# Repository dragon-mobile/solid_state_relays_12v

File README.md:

# Solid State Relays - 12Volts

<br/>

<br/>

The Solid State Relays - 12Volts is one of the open hardware solid state relay
PCB of my Dragon Mobile GitHub organization with a goal to make
useful hardware with associated firmware and software for the tiny home, van
life and maker communities.

## Visual 3D examples

Top view<br/>
<br/>
Bottom view<br/>
<br/>

## Description

The board consist of three main electronic sections: Power In,
Control In / Power Out,
and the Solid State Relays which are divided into two banks of four output
channels.
There are two mechanical sections as well: Mounting Holes, and the
eight MOSFET Mounting Access Holes.

### Power In

The main 12 volt power source for the rest of the board enters via the
JPWR1 and optional JPWR2 XT-60PW-M connectors. Each is rated for up to 35A but
may support 40-50A loads for brief periods in practice with good cooling.
Care should be taken to not connect or disconnect the power when any outputs
are active as this may cause some arcing within the connector which will
shorten its life span. This will be especially noticable with large inductive
loads.

The two Transient-Voltage-Suppression (TVS) diodes: TVSP1 and optional TVSP2
provide protection against high voltage spikes from entering the board through
the power source. Additionally they can act as reverse polarity protection by
shorting the incorrectly wiring source and blow its fuse. Care should be taken
to ensure the 12 volt wire is properly fused.

The two optional fan connectors: M1 and M2 are avalible to add optional cooling
fans which are always on or use external temperature / speed control.
If enclosed in a tight fitting case or cover it's recommended that at least one
fan be used to prevent hot spots that can cause premature component failure or
in extereme cases fires.

The final part of the Power In section is the highly recommended but optional
power applied/on LED circuit. The LEDP1 should light up any time power is
connected to the board to give a quick visual indicator. Optionally the onboard
LED can be replaced by connecting an external LED via the optional JP2 pin
header. Connecting both LEDP1 and an external LED is not recommended. R1 is the
current limiting resistor for the LED and can be replaced with 0Ω one when
an external resistor is used on the JP2 circuit.
By cutting the trace between the pads of JP1 the indicator circuit can be
disabled. Additionally by doing this and soldering two leads to the pads an
external switch could be used to turn the indicator on and off as needed.

#### Optional components

The board is design to supply 30-40A across all outputs without the addition
of JPWR2 and TVSP2 to save costs. For higher currents both the additional
connector and TVS should be used. It is also recommended you increase the
board copper plating to 3oz (105μm). An alternative but not recommended and
more risky way to increase current capacity is by soldering some point to point
jumper wires from near the power connectors and the center lead of the output
FETs and from the output of the FETs to the leads of the output connectors.

TVSP2 is the only surface mount component on the bottom side of the board.

### Control In / Power Out

This section provides the connectors JCNTL1 and JCNTL2 which interfaces the
control signals from the external circuits to the output FETs.
The external controls should be either electronic open drain (collector) or
mechanical switches which pull their output to ground when active.
The external controls may also switch between the +BATT voltage and ground but
an active low only signal is expected and preferred when possible.
Each connector is connected to a single bank of 4 output channels allowing each
one to be used with a different control if needed though a single control
connected to and controlling both is the expected configuration.

Additionally the connectors can each be used to supply power of +BATT volts at
1A max to external circuits.
Normally this is used to supply power to an external control boards like the
co-designed and recommended [picow_ssr_control] or [we_ssr_control] boards.

### Solid State Relays

This is the main section of the circuit board and contains most of the
components. There are 8 independent solid state relay circuits which are
designed to work the same. The relays outputs are laid out as two banks of
four channels each on the two longer edges of the board to allow easy access.
A single channel will be described next since other than their position and
names etc. the design is the same.

#### Channel description

The OUT1 channel will be used in this description. The switching (relay)
component is Q1 a P-channel IRF4905 MOSFET which electrical connects the +BATT
voltage to the output connector J1 (OUT1) when activated. The pullup resistor
RP1 keeps the FET off when there is no low input driving the gate via the
control input from the a1 pin of the JCNTL1 connector. The expected control
input is a open drain (collector) output which only actively drives the input
to ground and allows its output to float otherwise.

*Note* that Q1 is mounted on the bottom side of the board and bent over to
allow easy attachment to a large heat sink which is required. Look at the
picture of the bottom of the board in the Visual 3D examples section of this
README to better understand what it looks like when bent over for mounting.

** WARNING ** the metal tab and back of Q1 are at +BATT and need to be
electrically isolated from the heat sink if it is grounded while still
maintaining a good thermal contact.

The output is protected from most high voltage and reverse voltage spikes by
TVS1 a unidirectional Transient-Voltage-Suppression diode. It is mostly there
to protect against ESD and the voltage spikes commonly seens when switch off
inductive loads which could damage Q1 if they exceeded its own internal
protections.

The final three components: RL1, LED1, and the optional JL1 provide a quick
visual indicator for when the output is active. RL1 is the current limiting
resistor for the LED. Like with the power indicator circuit the indicator
circuit is all optional but highly recommended. When an LED is connected via
JL1 the internal LED should not be used.

### Mounting Holes

A US letter sized mounting template can be found in [MountingTemplate].

In a typical application the board will be mounted with brass or stainless
steel standoff which are tapped into a vertical aluminum, copper, or brass
backplate which also acts as the heat sink for the output FETs and all of
this is inside of a larger electrical enclosure or cabinet.
The mounting holes are sized for M3 hex (preferred) or round Male-Female ended
standoffs which should be 5-10mm high to allow the correct mounting of the
output FETs. the shortest standoff that doesn't cause the body to contact the
board and allow the legs to be bent at a right angle just pass the "neck" is
best.
In most cases this should be 5-6mm high but can end up as high as 10mm
depending on the insulators used.

The [picow_ssr_control] and [we_ssr_control] boards have been designed to mount
directly on top of / in front of this board with additional 20mm M-F standoffs
which would replace the normal M3 pan head screws used to secure the board at
H1, H4, and H5.

### MOSFET Mounting Access Holes

The last mechanical section are the access holes that were added to make
mounting the FET to an underlaying heat sink easier. They can also be found
on the [MountingTemplate]. On the template you will see outlines for a
typical silicone insulators.

*Note* one top corner of the HQ2 and HQ6 insulators may interfere with mounting
hole H5 and need to be trimmed back or bent up a little if flexible enough to
allow complete tighten of the standoff and not cause the board to bow up in the
middle. By using a magnetic screwdriver you should be able to pass the screw,
lock, and plastic shoulder washers through the holes in the board and FET to be
tighten down.
A little silicone or thermal grease can help keep the washers in place without
cause other issues.

## Contributing

Contributors are welcome.
Please note that this project has a [Contributor Covenant Code of Conduct].
By participating in this project you agree to abide by its terms.

All intentionally contributed hardware will be considered to be contributed
under the [CERN] license without any additional terms or conditions.

All intentionally contributed code will be considered to be contributed
under a [MIT] license without any additional terms or conditions.
Please include your information in a comment on all code files for the copyright
etc.

All intentionally contributed documentation, CAD files and libraries, footprints,
artwork or non-code text like this README etc. will be considered to be
contributed under the same [CC-BY-SA] license without any additional terms or
conditions.

Pull requests are always welcome. For major changes, please open an issue first
to discuss what you would like to change.
Please make sure to update or add tests as appropriate for all software changes.

## Licenses

<br/>

All hardware is licensed under the

  * [CERN] - CERN-OHL-W-2.0
  
You can find a copy of the CERN Open Hardware License - Weakly-reciprocal v2.0
in the [LICENSE-CERN-OHL-W-2] file and the how-to guide in the
[CERN-HOWTO_GUIDE] file.

All code is licensed under the

  * [MIT] - MIT License

You can find a copy of the license in the [LICENSE-MIT] file.

All documentation like this README is licensed under the Creative Commons
Attribution-ShareAlike 4.0 International License (CC-BY-SA).

All original CAD files and libraries, footprints, and artwork are also licensed
under the
Creative Commons Attribution-ShareAlike 4.0 International License (CC-BY-SA).
You can find a copy of the [CC-BY-SA] license in the [LICENSE-CC-BY-SA] file.

If after reading the above license files, how-tos, and related FAQs on the
linked license sites on how they apply to the project please either open an
issue or contact me (Michael Cummings) via my Github email and I will try
to guided you through my understanding of how it works.

[CC-BY-SA]: http://creativecommons.org/licenses/by-sa/4.0/
[CERN]: https://ohwr.org/project/cernohl/wikis/Documents/CERN-OHL-version-2
[CERN-HOWTO_GUIDE]: docs/cern_ohl_w_v2_howto.pdf
[Contributor Covenant Code of Conduct]: CODE_OF_CONDUCT.md 
[LICENSE-CC-BY-SA]: LICENSE-CC-BY-SA
[LICENSE-CERN-OHL-W-2]: CERN-OHL-W-2
[LICENSE-MIT]: LICENSE-MIT
[MIT]: https://opensource.org/licenses/MIT
[MountingTemplate]: docs/MountingTemplate.pdf
[picow_ssr_control]: https://github.com/dragon-mobile/picow_ssr_control
[we_ssr_control]: https://github.com/dragon-mobile/we_ssr_control

<hr>
Copyright &copy; 2022-2023, Michael Cummings<br/>

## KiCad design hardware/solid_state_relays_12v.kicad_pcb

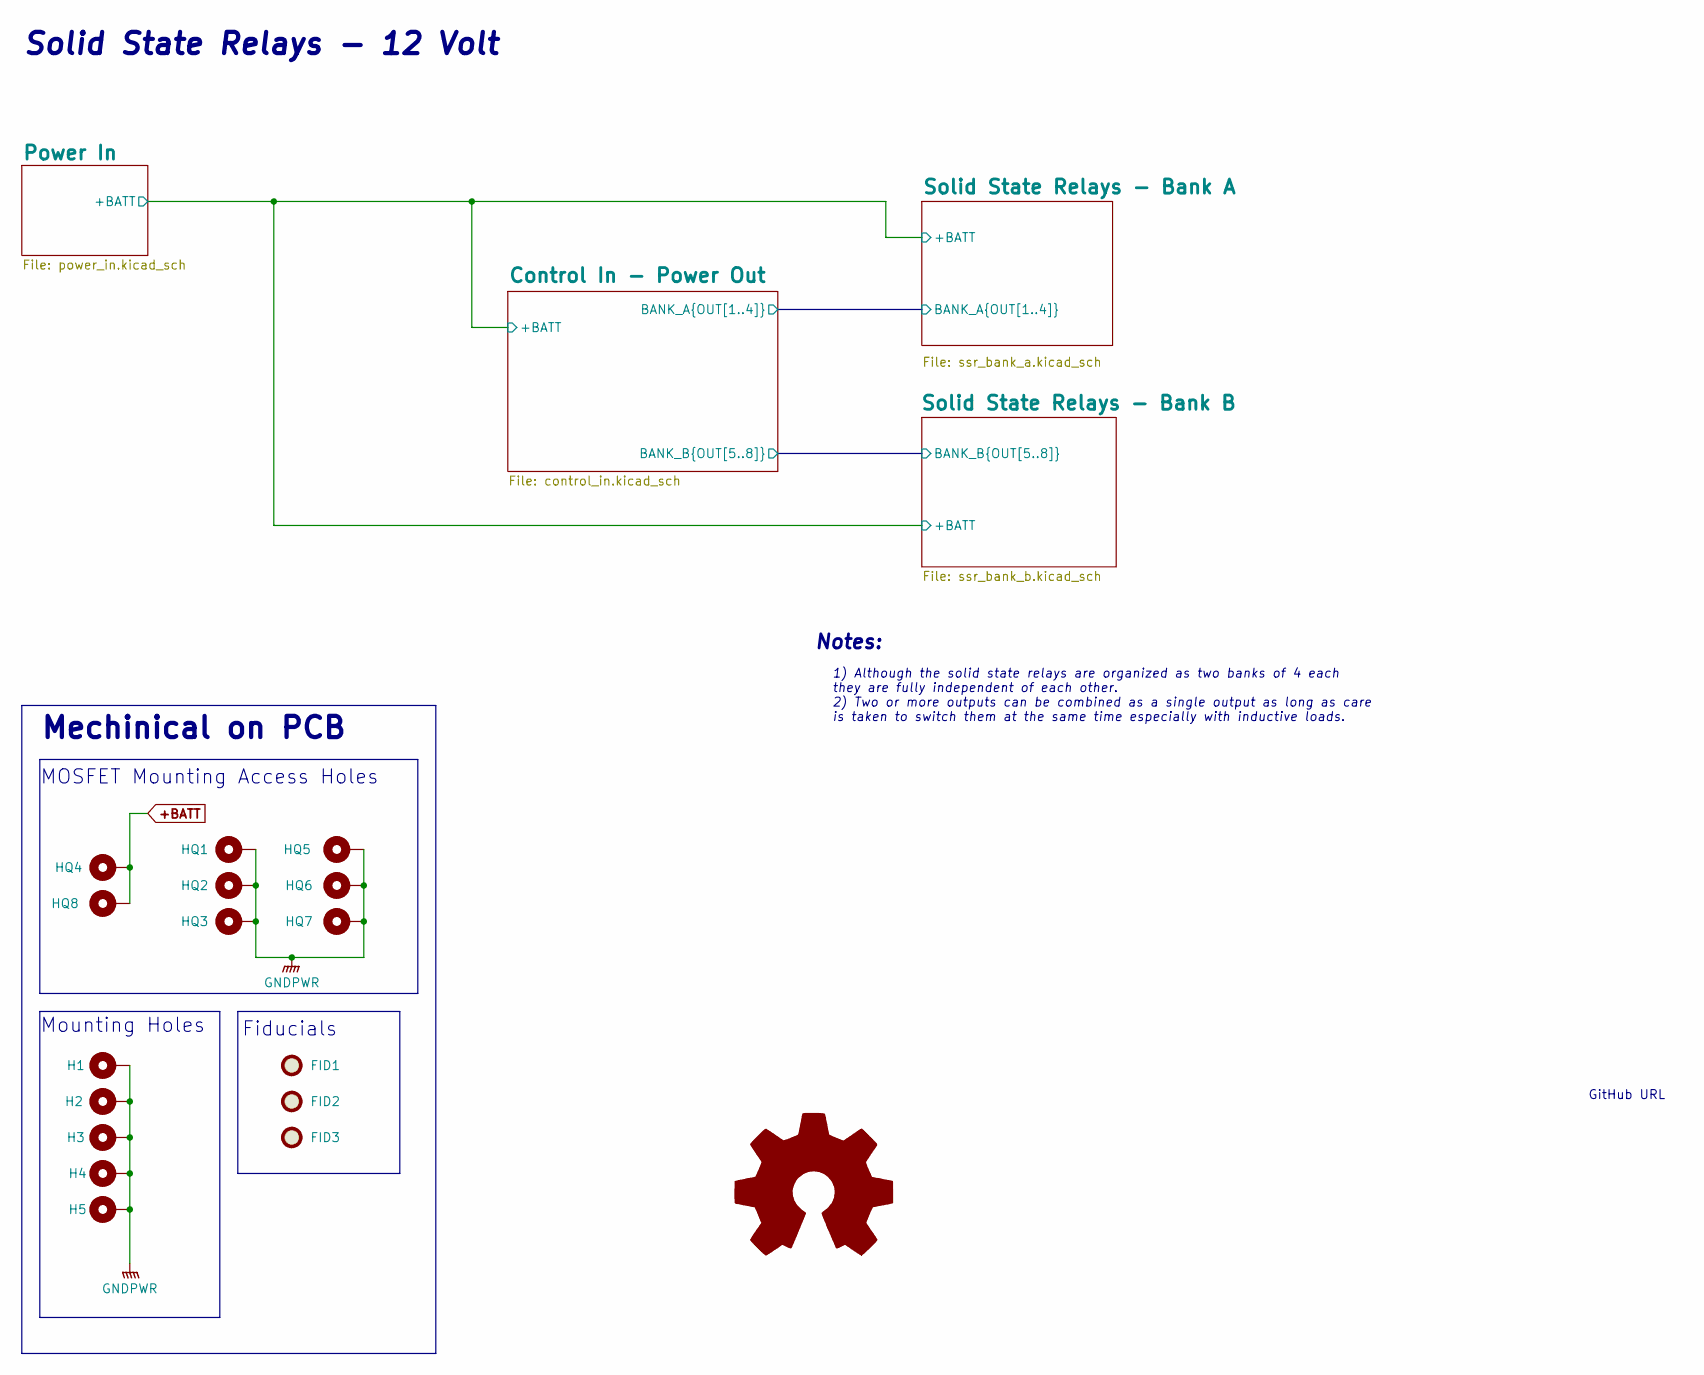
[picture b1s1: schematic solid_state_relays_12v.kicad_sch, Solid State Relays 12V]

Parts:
FID1, FID2, FID3: Fiducial; Fiducial_0.5mm_Mask1mm
H1, H2, H3, H4, H5: MountingHole; MountingHole_3.2mm_M3_Pad_Via
HQ1, HQ2, HQ3, HQ4, HQ5, HQ6, HQ7, HQ8: Access Hole; MountingHole_6.1mm_Pad_Via

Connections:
+BATT: HQ4.1, HQ8.1; also elsewhere on the board
GNDPWR: H1.1, H2.1, H3.1, H4.1, H5.1, HQ1.1, HQ2.1, HQ3.1, HQ5.1, HQ6.1, HQ7.1; also elsewhere on the board

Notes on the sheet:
MOSFET Mounting Access Holes
Fiducials
Solid State Relays - 12 Volt
Notes:
Mechinical on PCB
Mounting Holes
GitHub URL
1) Although the solid state relays are organized as two banks of 4 each they are fully independent of each other. 2) Two or more outputs can be combined as a single output as long as care is taken to switch them at the same time especially with inductive loads.

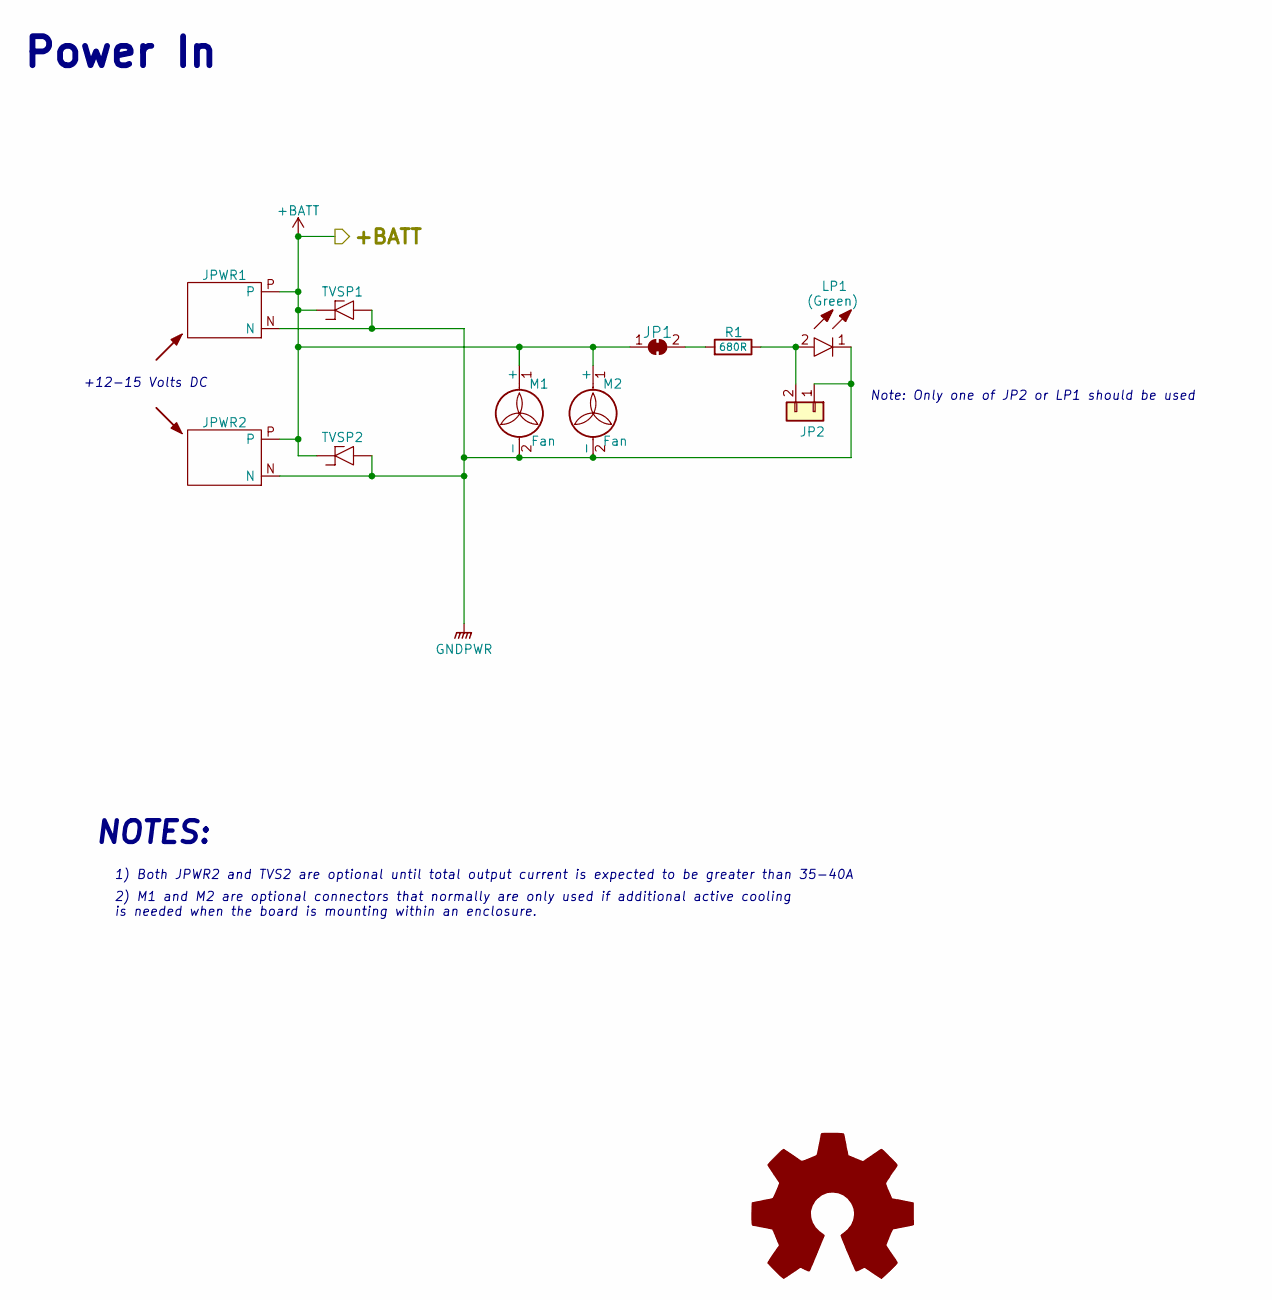
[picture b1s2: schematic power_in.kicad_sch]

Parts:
JP1: SolderJumper_2_Bridged; SolderJumper-2_P1.3mm_Bridged_RoundedPad1.0x1.5mm
JP2: Conn_01x02; PinHeader_1x02_P1.00mm_Vertical
JPWR1, JPWR2: XT60PW-M; XT60PWM
LP1: LTST-C190KGKT; LEDC1608X80N; Mouser Part Number 859-LTST-C190KGKT
M1, M2: Fan; PinHeader_1x02_P2.54mm_Vertical
R1: 680R; R_0805_2012Metric; Mouser Part Number 755-SDR10EZPJ681
TVSP1, TVSP2: SM6T18AY; Mouser Part Number 511-SM6T18AY

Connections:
+BATT: JP1.1 (A), JPWR1.P, JPWR2.P, M1.1 (+), M2.1 (+), TVSP1.1, TVSP2.1; also elsewhere on the board
GNDPWR: JP2.1, JPWR1.N, JPWR2.N, LP1.1, M1.2 (-), M2.2 (-), TVSP1.2, TVSP2.2; also elsewhere on the board
unnamed: JP1.2 (B), R1.2
unnamed: JP2.2, LP1.2, R1.1

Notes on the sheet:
Power In
Note: Only one of JP2 or LP1 should be used
1) Both JPWR2 and TVS2 are optional until total output current is expected to be greater than 35-40A
+12-15 Volts DC
2) M1 and M2 are optional connectors that normally are only used if additional active cooling is needed when the board is mounting within an enclosure.
NOTES:

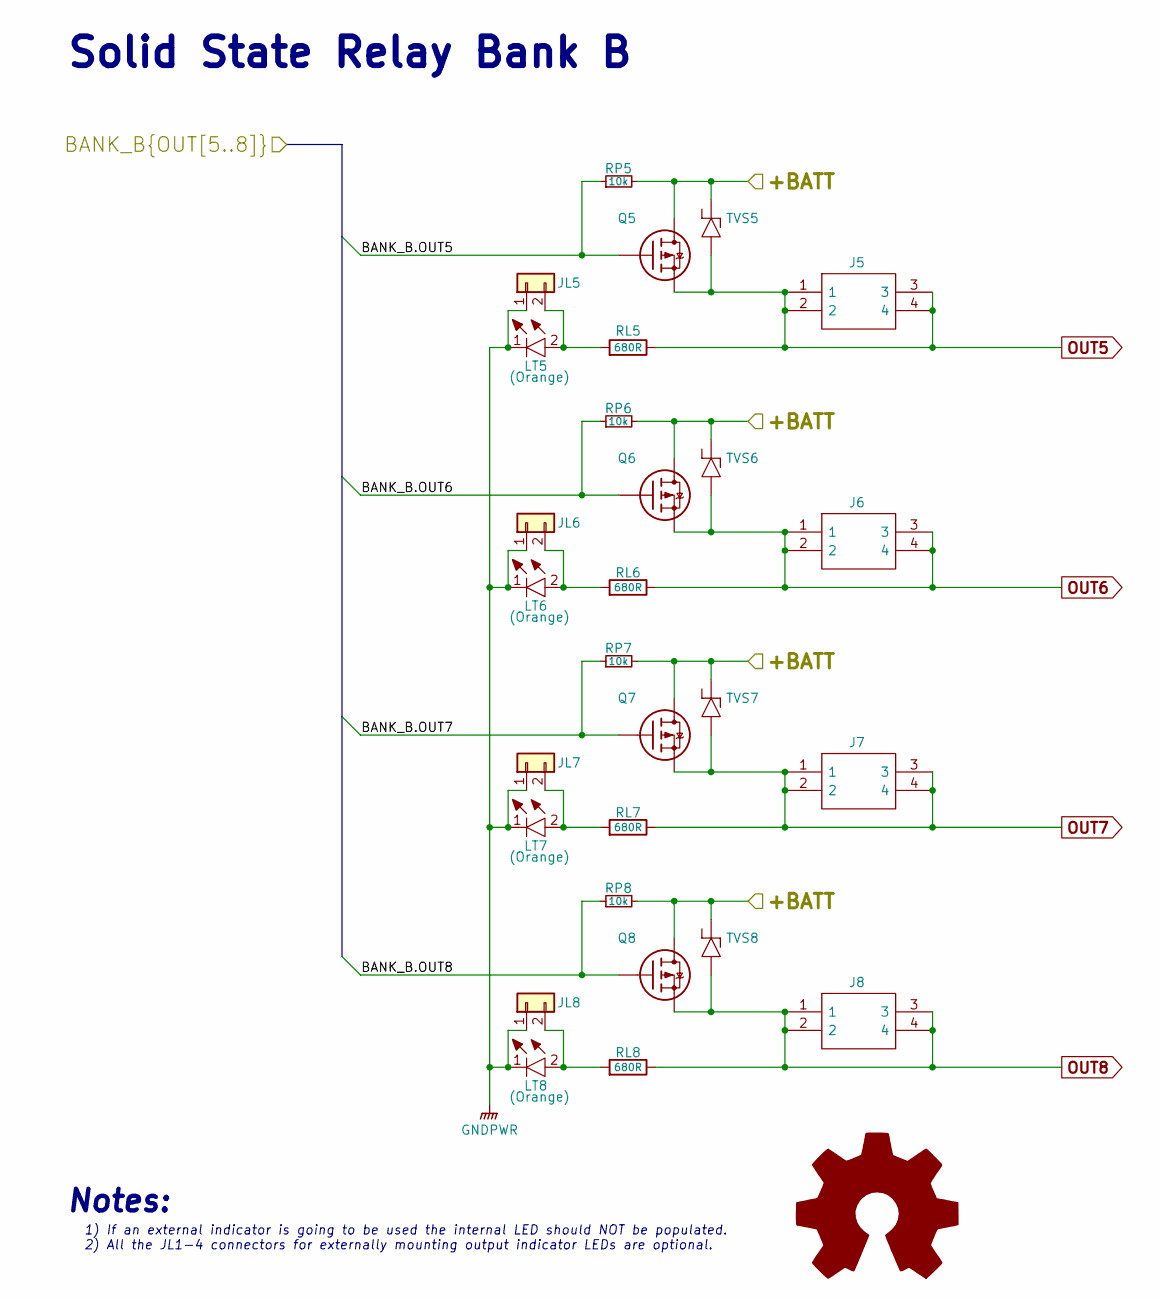
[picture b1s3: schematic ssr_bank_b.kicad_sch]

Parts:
J5, J6, J7, J8: 1190297; Mouser Part Number 651-1190297
JL5, JL6, JL7, JL8: Conn_01x02; PinHeader_1x02_P1.00mm_Vertical
LT5, LT6, LT7, LT8: LTST-C190KFKT; LEDC1607X80N; Mouser Part Number 859-LTST-C190KFKT
Q5, Q6, Q7, Q8: IRF4905PBF; Mouser Part Number 942-IRF4905PBF
RL5, RL6, RL7, RL8: 680R; R_0805_2012Metric; Mouser Part Number 755-SDR10EZPJ681
RP5, RP6, RP7, RP8: 10k; R_0603_1608Metric
TVS5, TVS6, TVS7, TVS8: SM6T18AY; Mouser Part Number 511-SM6T18AY

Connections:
+BATT: Q5.2, Q6.2, Q7.2, Q8.2, RP5.2, RP6.2, RP7.2, RP8.2, TVS5.1, TVS6.1, TVS7.1, TVS8.1; also elsewhere on the board
/Control In - Power Out/BANK_B.OUT5: Q5.1, RP5.1; also elsewhere on the board
/Control In - Power Out/BANK_B.OUT6: Q6.1, RP6.1; also elsewhere on the board
/Control In - Power Out/BANK_B.OUT7: Q7.1, RP7.1; also elsewhere on the board
/Control In - Power Out/BANK_B.OUT8: Q8.1, RP8.1; also elsewhere on the board
GNDPWR: JL5.1, JL6.1, JL7.1, JL8.1, LT5.1, LT6.1, LT7.1, LT8.1; also elsewhere on the board
unnamed: JL5.2, LT5.2, RL5.2
unnamed: JL6.2, LT6.2, RL6.2
unnamed: JL7.2, LT7.2, RL7.2
unnamed: JL8.2, LT8.2, RL8.2
OUT5: J5.1, J5.2, J5.3, J5.4, Q5.3, RL5.1, TVS5.2
OUT6: J6.1, J6.2, J6.3, J6.4, Q6.3, RL6.1, TVS6.2
OUT7: J7.1, J7.2, J7.3, J7.4, Q7.3, RL7.1, TVS7.2
OUT8: J8.1, J8.2, J8.3, J8.4, Q8.3, RL8.1, TVS8.2

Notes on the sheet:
Notes:
Solid State Relay Bank B
1) If an external indicator is going to be used the internal LED should NOT be populated. 2) All the JL1-4 connectors for externally mounting output indicator LEDs are optional.

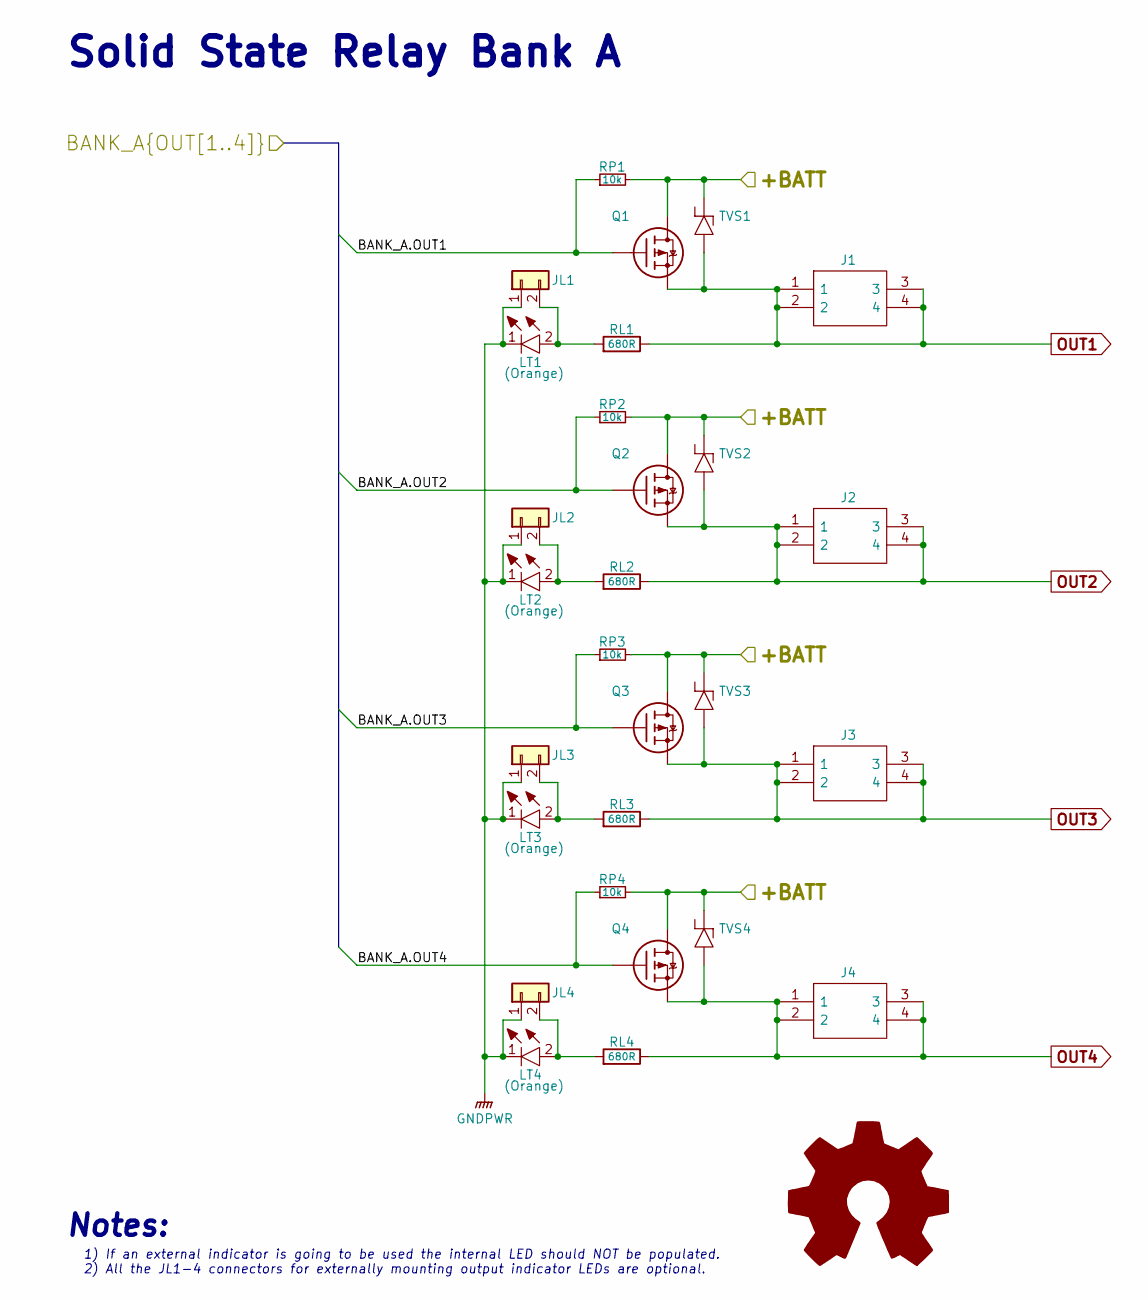
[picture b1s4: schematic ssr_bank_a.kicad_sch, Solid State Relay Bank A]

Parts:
J1, J2, J3, J4: 1190297; Mouser Part Number 651-1190297
JL1, JL2, JL3, JL4: Conn_01x02; PinHeader_1x02_P1.00mm_Vertical
LT1, LT2, LT3, LT4: LTST-C190KFKT; LEDC1607X80N; Mouser Part Number 859-LTST-C190KFKT
Q1, Q2, Q3, Q4: IRF4905PBF; Mouser Part Number 942-IRF4905PBF
RL1, RL2, RL3, RL4: 680R; R_0805_2012Metric; Mouser Part Number 755-SDR10EZPJ681
RP1, RP2, RP3, RP4: 10k; R_0603_1608Metric
TVS1, TVS2, TVS3, TVS4: SM6T18AY; Mouser Part Number 511-SM6T18AY

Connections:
+BATT: Q1.2, Q2.2, Q3.2, Q4.2, RP1.2, RP2.2, RP3.2, RP4.2, TVS1.1, TVS2.1, TVS3.1, TVS4.1; also elsewhere on the board
/Control In - Power Out/BANK_A.OUT1: Q1.1, RP1.1; also elsewhere on the board
/Control In - Power Out/BANK_A.OUT2: Q2.1, RP2.1; also elsewhere on the board
/Control In - Power Out/BANK_A.OUT3: Q3.1, RP3.1; also elsewhere on the board
/Control In - Power Out/BANK_A.OUT4: Q4.1, RP4.1; also elsewhere on the board
GNDPWR: JL1.1, JL2.1, JL3.1, JL4.1, LT1.1, LT2.1, LT3.1, LT4.1; also elsewhere on the board
unnamed: JL1.2, LT1.2, RL1.2
unnamed: JL2.2, LT2.2, RL2.2
unnamed: JL3.2, LT3.2, RL3.2
unnamed: JL4.2, LT4.2, RL4.2
OUT1: J1.1, J1.2, J1.3, J1.4, Q1.3, RL1.1, TVS1.2
OUT2: J2.1, J2.2, J2.3, J2.4, Q2.3, RL2.1, TVS2.2
OUT3: J3.1, J3.2, J3.3, J3.4, Q3.3, RL3.1, TVS3.2
OUT4: J4.1, J4.2, J4.3, J4.4, Q4.3, RL4.1, TVS4.2

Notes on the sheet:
Notes:
Solid State Relay Bank A
1) If an external indicator is going to be used the internal LED should NOT be populated. 2) All the JL1-4 connectors for externally mounting output indicator LEDs are optional.

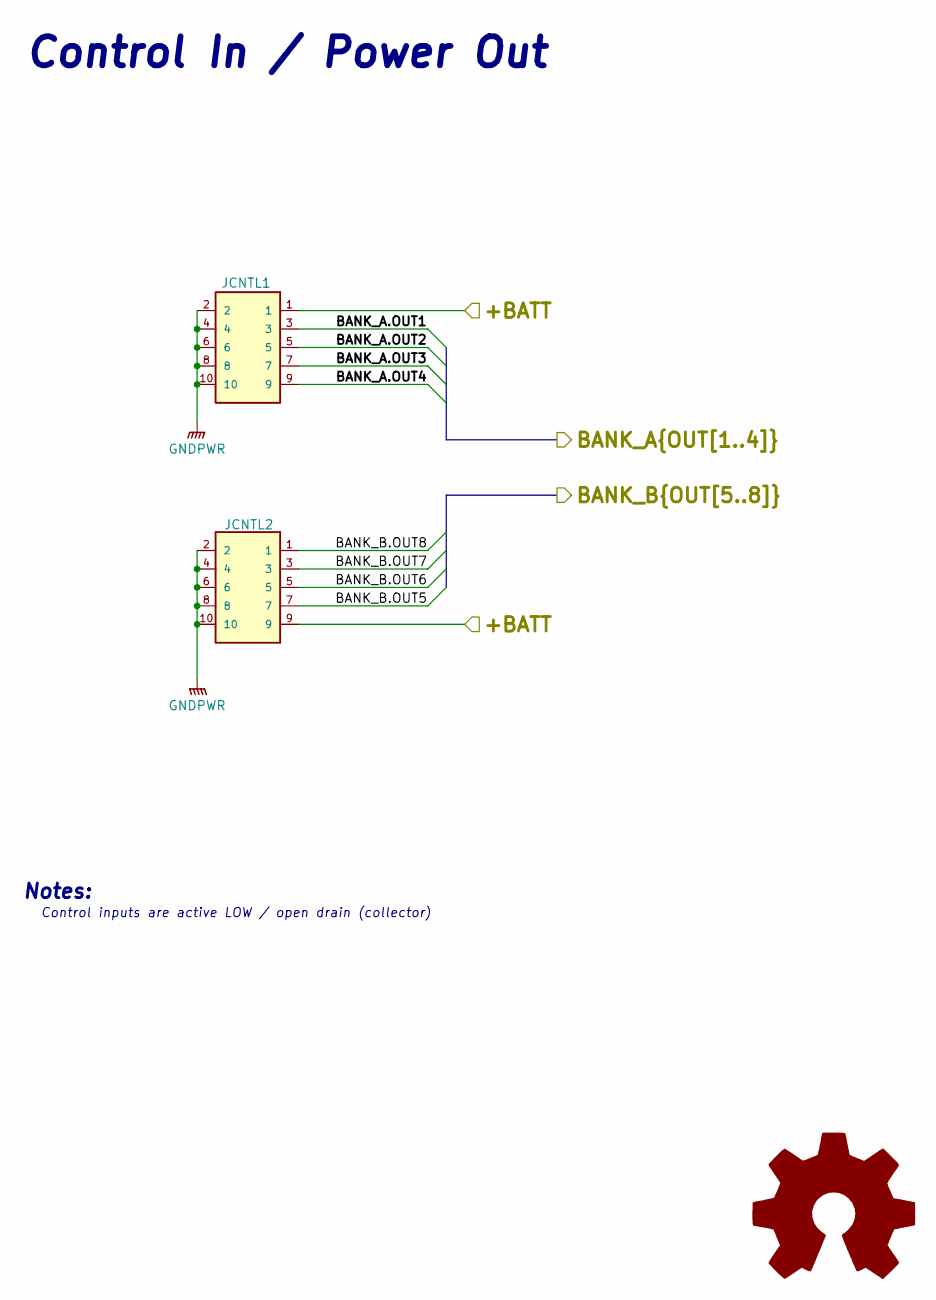
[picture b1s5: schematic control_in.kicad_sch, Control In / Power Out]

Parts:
JCNTL1, JCNTL2: SHF-105-01-L-D-RA; SAMTEC_SHF-105-01-L-D-RA; Mouser Part Number 200-SHF10501LDRATR

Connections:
+BATT: JCNTL1.1, JCNTL2.9; also elsewhere on the board
/Control In - Power Out/BANK_A.OUT1: JCNTL1.3; also elsewhere on the board
/Control In - Power Out/BANK_A.OUT2: JCNTL1.5; also elsewhere on the board
/Control In - Power Out/BANK_A.OUT3: JCNTL1.7; also elsewhere on the board
/Control In - Power Out/BANK_A.OUT4: JCNTL1.9; also elsewhere on the board
/Control In - Power Out/BANK_B.OUT5: JCNTL2.7; also elsewhere on the board
/Control In - Power Out/BANK_B.OUT6: JCNTL2.5; also elsewhere on the board
/Control In - Power Out/BANK_B.OUT7: JCNTL2.3; also elsewhere on the board
/Control In - Power Out/BANK_B.OUT8: JCNTL2.1; also elsewhere on the board
GNDPWR: JCNTL1.2, JCNTL1.4, JCNTL1.6, JCNTL1.8, JCNTL1.10, JCNTL2.2, JCNTL2.4, JCNTL2.6, JCNTL2.8, JCNTL2.10; also elsewhere on the board

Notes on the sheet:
Notes:
Control inputs are active LOW / open drain (collector)
Control In / Power Out

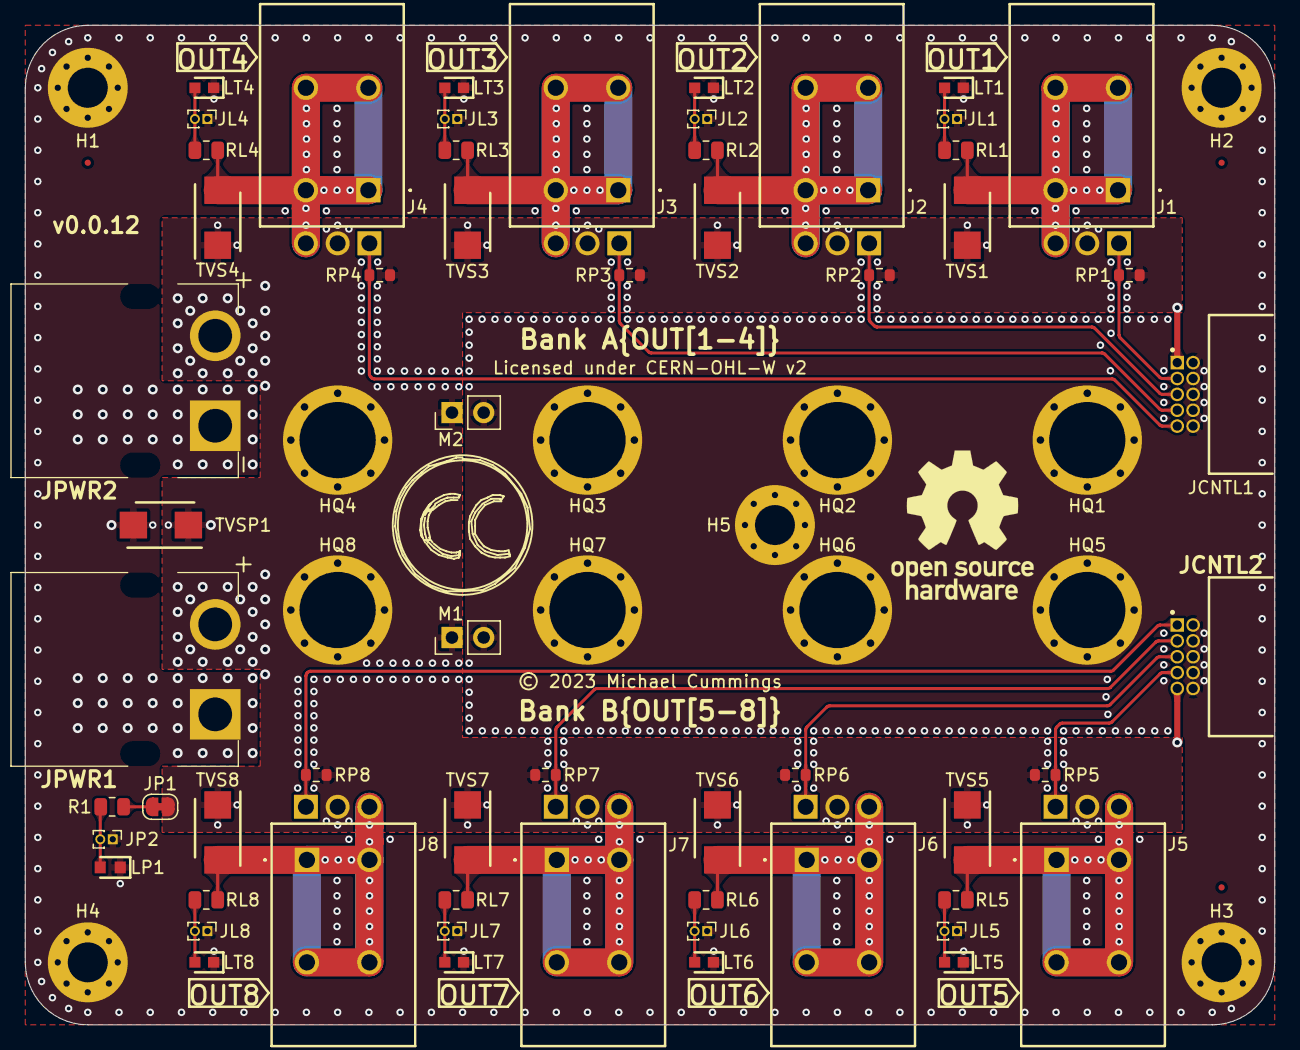
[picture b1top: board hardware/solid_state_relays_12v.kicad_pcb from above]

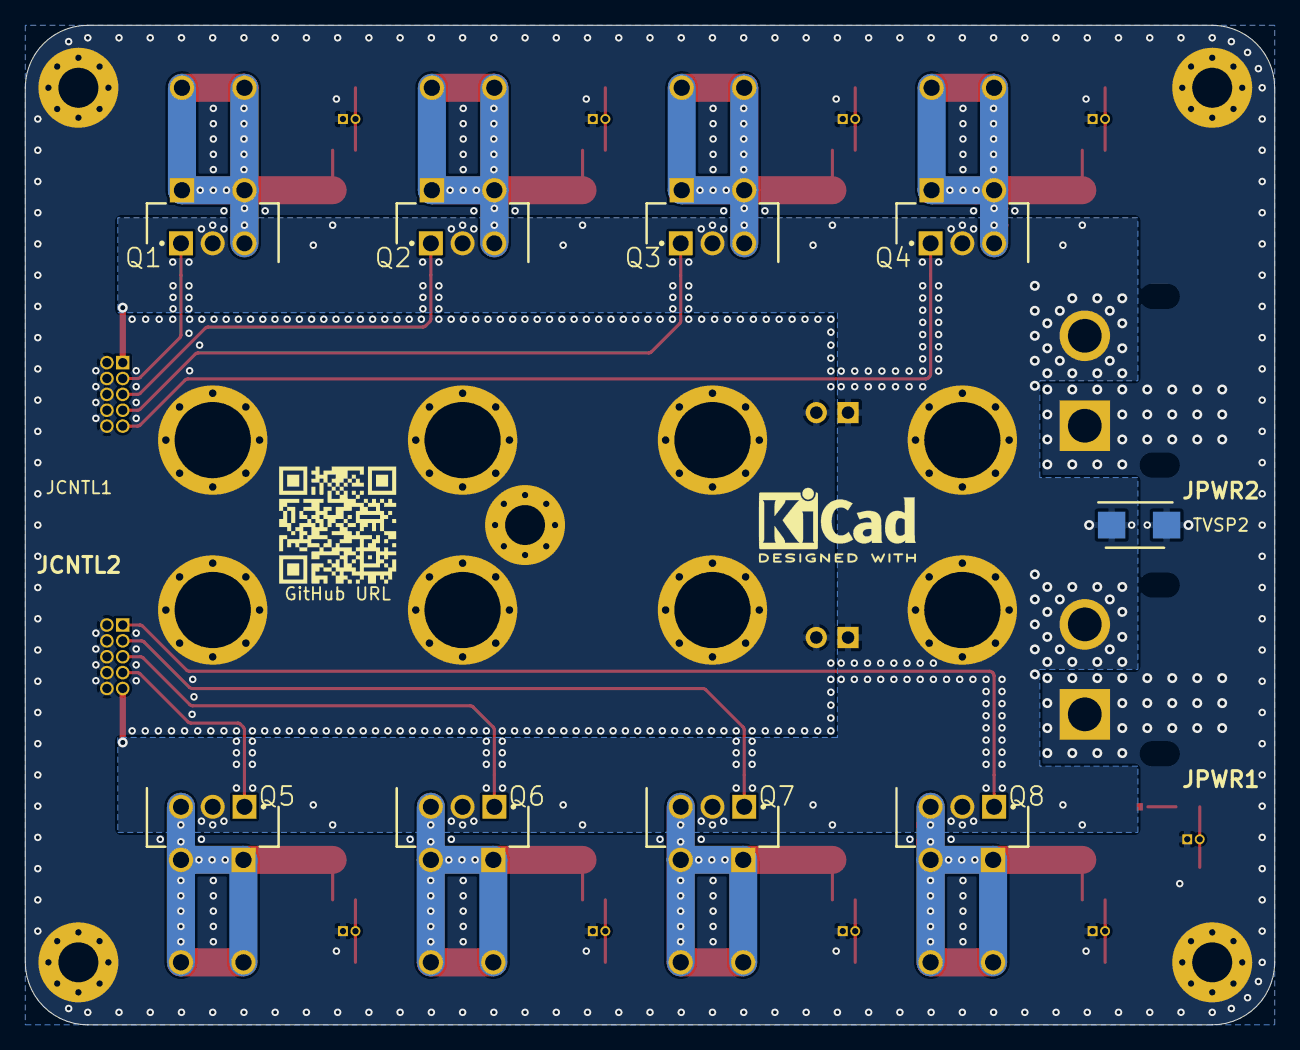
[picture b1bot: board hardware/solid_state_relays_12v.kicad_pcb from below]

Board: 2 copper layers, 100.0 x 80.0 mm, 94 parts (9 on the bottom side), 28 nets.

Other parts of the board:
JCNTL1_Label: JCNTL1_Label
JCNTL2_Label: JCNTL2_Label
OUT1: OUT1; OUT
OUT2: OUT2; OUT
OUT3: OUT3; OUT
OUT4: OUT4; OUT
OUT5: OUT5; OUT
OUT6: OUT6; OUT
OUT7: OUT7; OUT
OUT8: OUT8; OUT

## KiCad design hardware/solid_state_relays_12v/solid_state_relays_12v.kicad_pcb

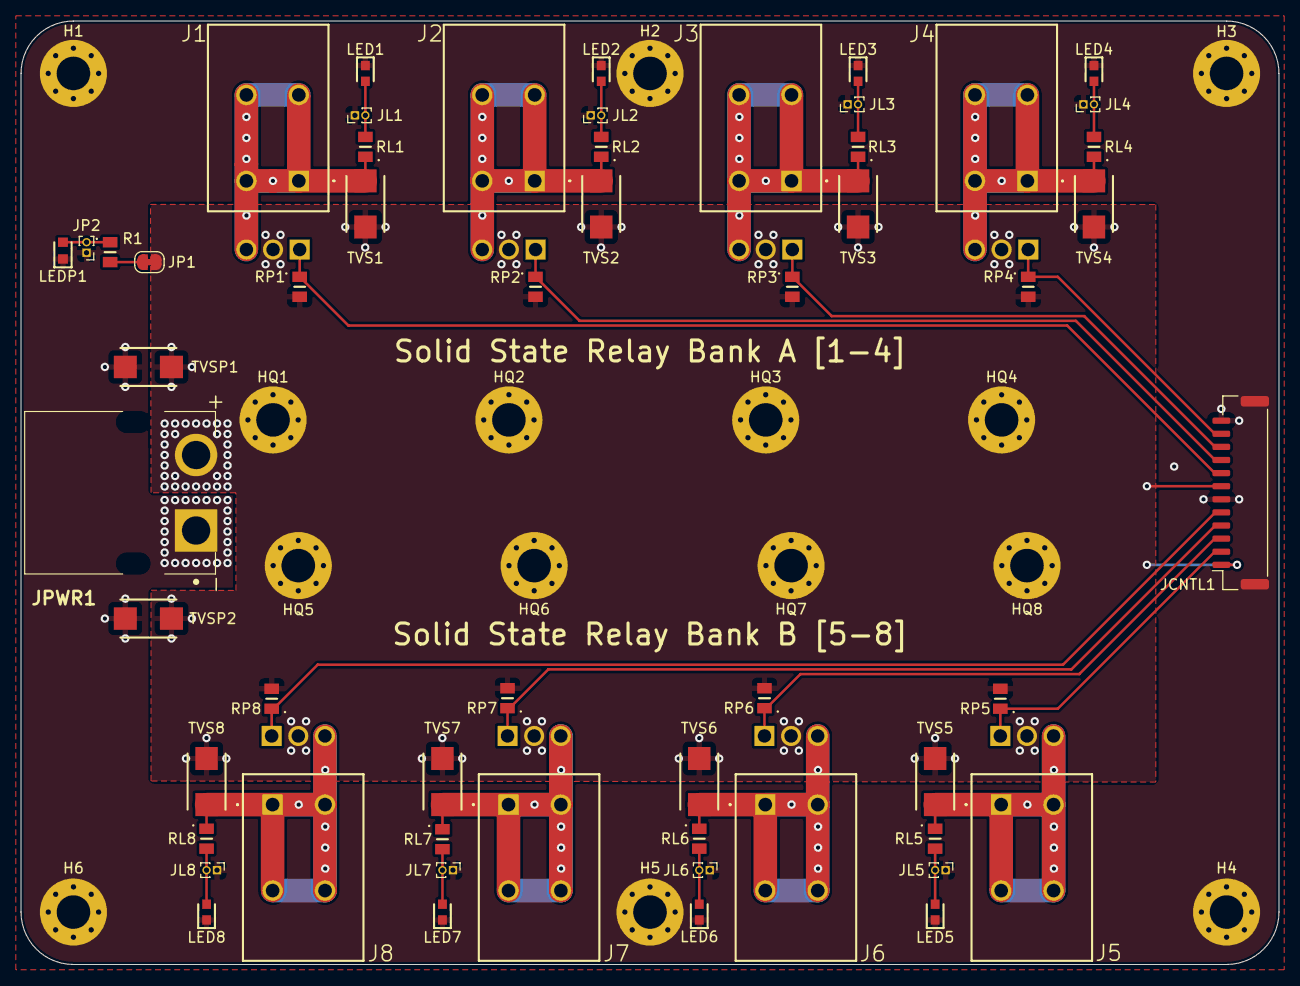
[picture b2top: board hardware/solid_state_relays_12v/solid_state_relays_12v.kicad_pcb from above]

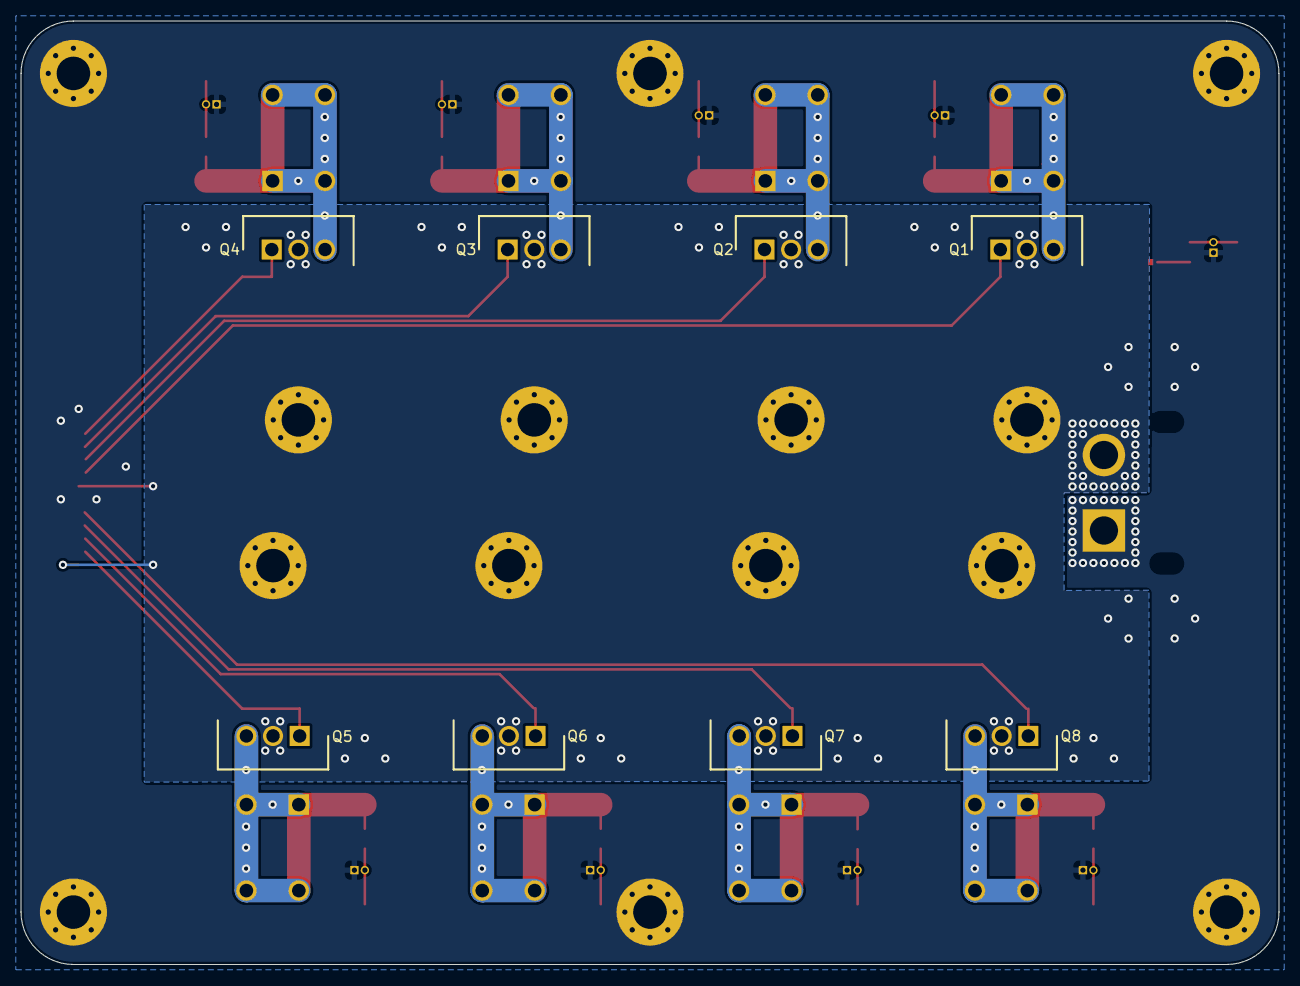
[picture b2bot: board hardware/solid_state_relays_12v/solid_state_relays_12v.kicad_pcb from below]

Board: 2 copper layers, 120.0 x 90.0 mm, 78 parts (8 on the bottom side), 28 nets.

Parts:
H1, H2, H3, H4, H5, H6: MountingHole; MountingHole_3.2mm_M3_Pad_Via
HQ1, HQ2, HQ3, HQ4, HQ5, HQ6, HQ7, HQ8: HeatsinkHole; MountingHole_3.2mm_M3_Pad_Via
J1, J2, J3, J4, J5, J6, J7, J8: 1190297
JCNTL1: Conn_01x12; JST_GH_SM12B-GHS-TB_1x12-1MP_P1.25mm_Horizontal
JL1, JL2, JL3, JL4, JL5, JL6, JL7, JL8: Conn_01x02; PinHeader_1x02_P1.00mm_Vertical
JP1: SolderJumper_2_Bridged; SolderJumper-2_P1.3mm_Bridged_RoundedPad1.0x1.5mm
JP2: Conn_01x02; PinHeader_1x02_P1.00mm_Vertical
JPWR1: XT60PW-M; XT60PWM
LED1, LED2, LED3, LED4, LED5, LED6, LED7, LED8: LTST-C190KFKT; LEDC1607X80N
LEDP1: LTST-C190KGKT; LEDC1608X80N
Q1, Q2, Q3, Q4, Q5, Q6, Q7, Q8: IRF4905PBF; TO254P469X1042X1967-3P
R1: 1k5; RESC2012X65N
RL1, RL2, RL3, RL4, RL5, RL6, RL7, RL8: 1k5; RESC2012X65N
RP1, RP2, RP3, RP4, RP5, RP6, RP7, RP8: 10k; RESC2012X65N
TVS1, TVS2, TVS3, TVS4, TVS5, TVS6, TVS7, TVS8: SM6T30AY; SMBJ36CATR
TVSP1, TVSP2: SM6T30AY; SMBJ36CATR

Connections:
+BATT: HQ1.1, HQ2.1, HQ3.1, HQ4.1, HQ5.1, HQ6.1, HQ7.1, HQ8.1, JCNTL1.1, JCNTL1.7, JP1.1 (A), JPWR1.P, Q1.2, Q2.2, Q3.2, Q4.2, Q5.2, Q6.2, Q7.2, Q8.2, RP1.2, RP2.2, RP3.2, RP4.2, RP5.2, RP6.2, RP7.2, RP8.2, TVS1.1, TVS2.1, TVS3.1, TVS4.1, TVS5.1, TVS6.1, TVS7.1, TVS8.1, TVSP1.1, TVSP2.1
/a1: JCNTL1.8, Q1.1, RP1.1
/a2: JCNTL1.9, Q2.1, RP2.1
/a3: JCNTL1.10, Q3.1, RP3.1
/a4: JCNTL1.11, Q4.1, RP4.1
/a5: JCNTL1.2, Q5.1, RP5.1
/a6: JCNTL1.3, Q6.1, RP6.1
/a7: JCNTL1.4, Q7.1, RP7.1
/a8: JCNTL1.5, Q8.1, RP8.1
GNDPWR: H1.1, H2.1, H3.1, H4.1, H5.1, H6.1, JCNTL1.6, JCNTL1.12, JCNTL1.MP (Mounting_pad_1), JL1.1, JL2.1, JL3.1, JL4.1, JL5.1, JL6.1, JL7.1, JL8.1, JP2.1, JPWR1.N, LED1.1, LED2.1, LED3.1, LED4.1, LED5.1, LED6.1, LED7.1, LED8.1, LEDP1.1, TVSP1.2, TVSP2.2
unnamed: JL1.2, LED1.2, RL1.2
unnamed: JL2.2, LED2.2, RL2.2
unnamed: JL3.2, LED3.2, RL3.2
unnamed: JL4.2, LED4.2, RL4.2
unnamed: JL5.2, LED5.2, RL5.2
unnamed: JL6.2, LED6.2, RL6.2
unnamed: JL7.2, LED7.2, RL7.2
unnamed: JL8.2, LED8.2, RL8.2
unnamed: JP1.2 (B), R1.2
unnamed: JP2.2, LEDP1.2, R1.1
OUT1: J1.1, J1.2, J1.3, J1.4, Q1.3, RL1.1, TVS1.2
OUT2: J2.1, J2.2, J2.3, J2.4, Q2.3, RL2.1, TVS2.2
OUT3: J3.1, J3.2, J3.3, J3.4, Q3.3, RL3.1, TVS3.2
OUT4: J4.1, J4.2, J4.3, J4.4, Q4.3, RL4.1, TVS4.2
OUT5: J5.1, J5.2, J5.3, J5.4, Q5.3, RL5.1, TVS5.2
OUT6: J6.1, J6.2, J6.3, J6.4, Q6.3, RL6.1, TVS6.2
OUT7: J7.1, J7.2, J7.3, J7.4, Q7.3, RL7.1, TVS7.2
OUT8: J8.1, J8.2, J8.3, J8.4, Q8.3, RL8.1, TVS8.2

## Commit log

2022-08-22 Updated README.md for project
2022-08-22 Updated README.md for project 2
2022-08-22 Updated README.md for project 3
2022-08-27 Re-worked directory structure of project
2022-12-03 WIP control connector changes
2022-12-22 Updated connectors and improved ground plane for control signals
2023-01-04 Misc updates mostly related to Silkscreen and adding draft production output
2023-01-07 Started writing description in README
2023-01-07 Additional text in README
2023-01-08 Completed more documentation in README
2023-01-09 Completed more documentation for mechanical sections in README and update MountingTemplate
2023-01-09 Completed more documentation for mechanical sections in README
2023-01-09 Make some corections and additions to Mounting.Template layer
2023-01-09 Adding some 3D models of components
2023-01-09 Edits in mechanical sections of README
2023-01-10 Updated PCB images
2023-01-10 Updated rev. to v0.0.8
2023-01-10 Updated production files for rev.
2023-01-10 Updated PCB images again
2023-01-10 One more try to get correct PCB PNGs
2023-01-10 One more try to get correct PNGs for v0.0.9
2023-01-10 Updated production files for v0.0.9
2023-01-22 Added power header pins for fans
2023-01-22 Updated docs for fan power header pins
2023-01-27 Changed schematic to hierarchical style with mutliple sheets
2023-02-09 Via spamming #1
2023-02-13 Pre KiCad 7.0.0 WIP
2023-02-13 Added share_components submodule
2023-03-16 Commit before removing git submodules
2023-03-16 Commit removing git submodules

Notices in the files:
README.md:
https://img.shields.io/static/v1?label=license&message=CERN-OHL-W-2.0%20%2F%20MIT%20%2F%20CC-BY-SA-4.0&color=orange
CC BY-SA 4.0
hardware/control_in.kicad_sch:
License: CC By SA 4.0
Hardware License: CERN-OHL-W
hardware/solid_state_relays_12v.kicad_pcb:
creativecommons.org/licenses/by/4.0
License: CC By 4.0
© 2023 Michael Cummings
Licensed under CERN-OHL-W v2
